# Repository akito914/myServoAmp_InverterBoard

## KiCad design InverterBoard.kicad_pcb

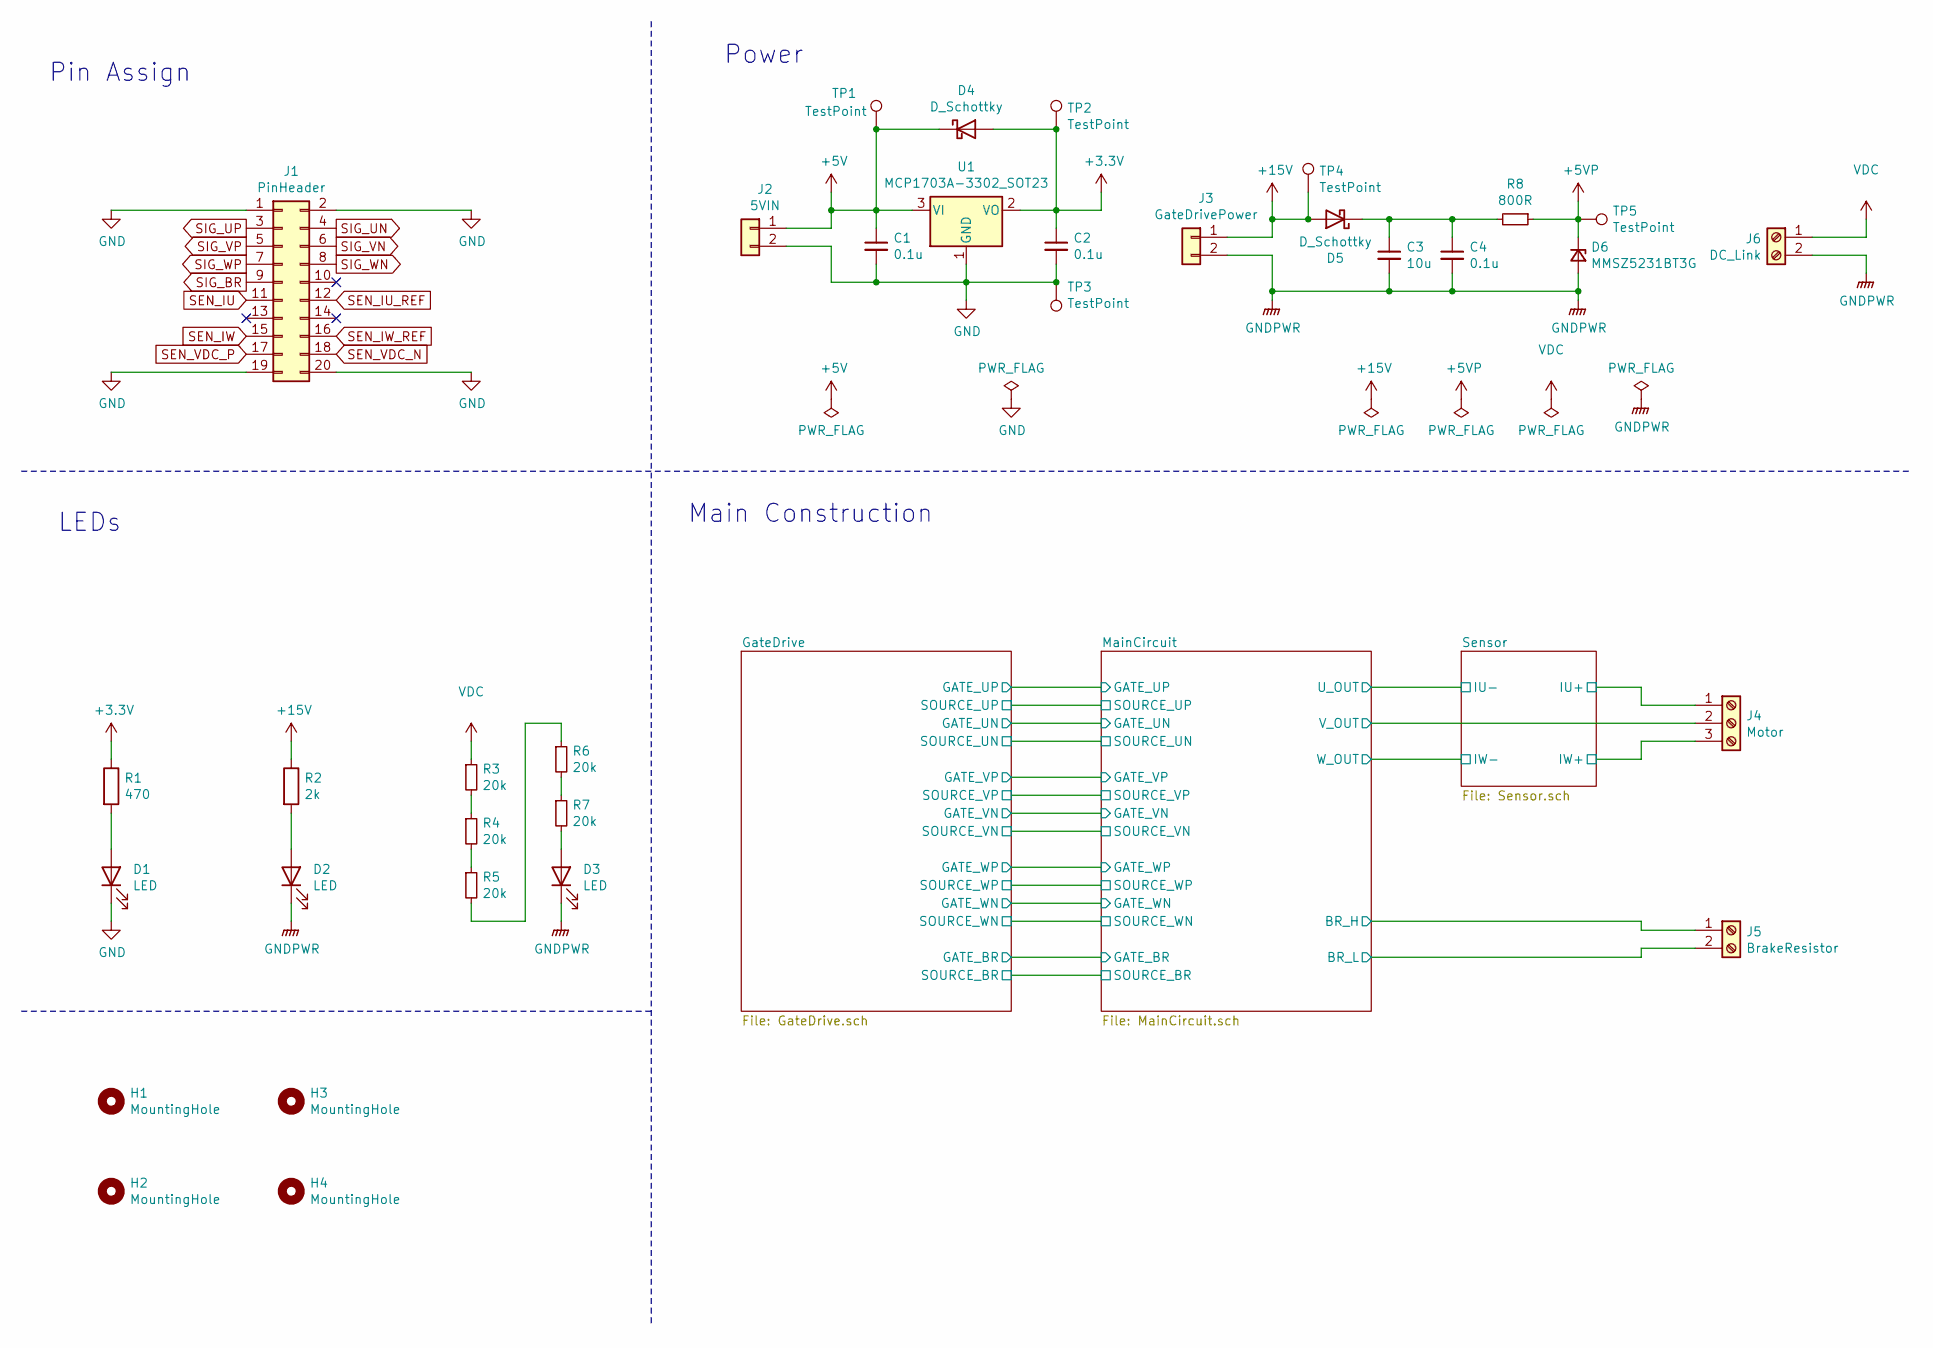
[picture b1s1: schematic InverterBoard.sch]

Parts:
C1, C2, C4: 0.1u; C_0603_1608Metric
C3: 10u; C_0805_2012Metric
D1, D2, D3: LED; LED_0603_1608Metric
D4, D5: D_Schottky; D_SOD-123
D6: MMSZ5231BT3G; D_SOD-123
H1, H2, H3, H4: MountingHole; MountingHole_3.2mm_M3
J1: PinHeader; IDC-Header_2x10_P2.54mm_Vertical
J2: 5VIN; JST_XH_S2B-XH-A-1_1x02_P2.50mm_Horizontal
J3: GateDrivePower; JST_XH_S2B-XH-A-1_1x02_P2.50mm_Horizontal
J4: Motor; JST_VH_B3PS-VH_1x03_P3.96mm_Horizontal
J5: BrakeResistor; JST_VH_B2PS-VH_1x02_P3.96mm_Horizontal
J6: DC_Link; JST_VH_B2PS-VH_1x02_P3.96mm_Horizontal
R1: 470; R_0603_1608Metric
R2: 2k; R_0603_1608Metric
R3, R4, R5, R6, R7: 20k; R_0603_1608Metric
R8: 800R; R_0603_1608Metric
TP1, TP2, TP3, TP4: TestPoint; TestPoint_Loop_D2.50mm_Drill1.0mm_LowProfile
TP5: TestPoint; TestPoint_Pad_D1.0mm
U1: MCP1703A-3302_SOT23; SOT-23

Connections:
+3V3: C2.1, D4.2 (A), R1.1, TP2.1, U1.2 (VO); also elsewhere on the board
+5V: C1.1, D4.1 (K), J2.1, TP1.1, U1.3 (VI)
+5VP: D6.1 (K), R8.1, TP5.1; also elsewhere on the board
+15V: D5.2 (A), J3.1, R2.1, TP4.1; also elsewhere on the board
/GateDrive/SOURCE_VP: J4.2; also elsewhere on the board
/MainCircuit/BR_L: J5.2; also elsewhere on the board
/Sensor/IU+: J4.1; also elsewhere on the board
/Sensor/IW+: J4.3; also elsewhere on the board
GND: C1.2, C2.2, D1.1 (K), J1.1, J1.2, J1.19, J1.20, J2.2, TP3.1, U1.1 (GND); also elsewhere on the board
GNDPWR: C3.2, C4.2, D2.1 (K), D3.1 (K), D6.2 (A), J3.2, J6.2; also elsewhere on the board
unnamed: C3.1, C4.1, D5.1 (K), R8.2
unnamed: D1.2 (A), R1.2
unnamed: D2.2 (A), R2.2
unnamed: D3.2 (A), R7.2
unnamed: R3.2, R4.1
unnamed: R4.2, R5.1
unnamed: R5.2, R6.1
unnamed: R6.2, R7.1
SEN_IU: J1.11; also elsewhere on the board
SEN_IU_REF: J1.12; also elsewhere on the board
SEN_IW: J1.15; also elsewhere on the board
SEN_IW_REF: J1.16; also elsewhere on the board
SEN_VDC_N: J1.18; also elsewhere on the board
SEN_VDC_P: J1.17; also elsewhere on the board
SIG_BR: J1.9; also elsewhere on the board
SIG_UN: J1.4; also elsewhere on the board
SIG_UP: J1.3; also elsewhere on the board
SIG_VN: J1.6; also elsewhere on the board
SIG_VP: J1.5; also elsewhere on the board
SIG_WN: J1.8; also elsewhere on the board
SIG_WP: J1.7; also elsewhere on the board
VDC: J5.1, J6.1, R3.1; also elsewhere on the board

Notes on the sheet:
Power
Main Construction
Pin Assign
LEDs

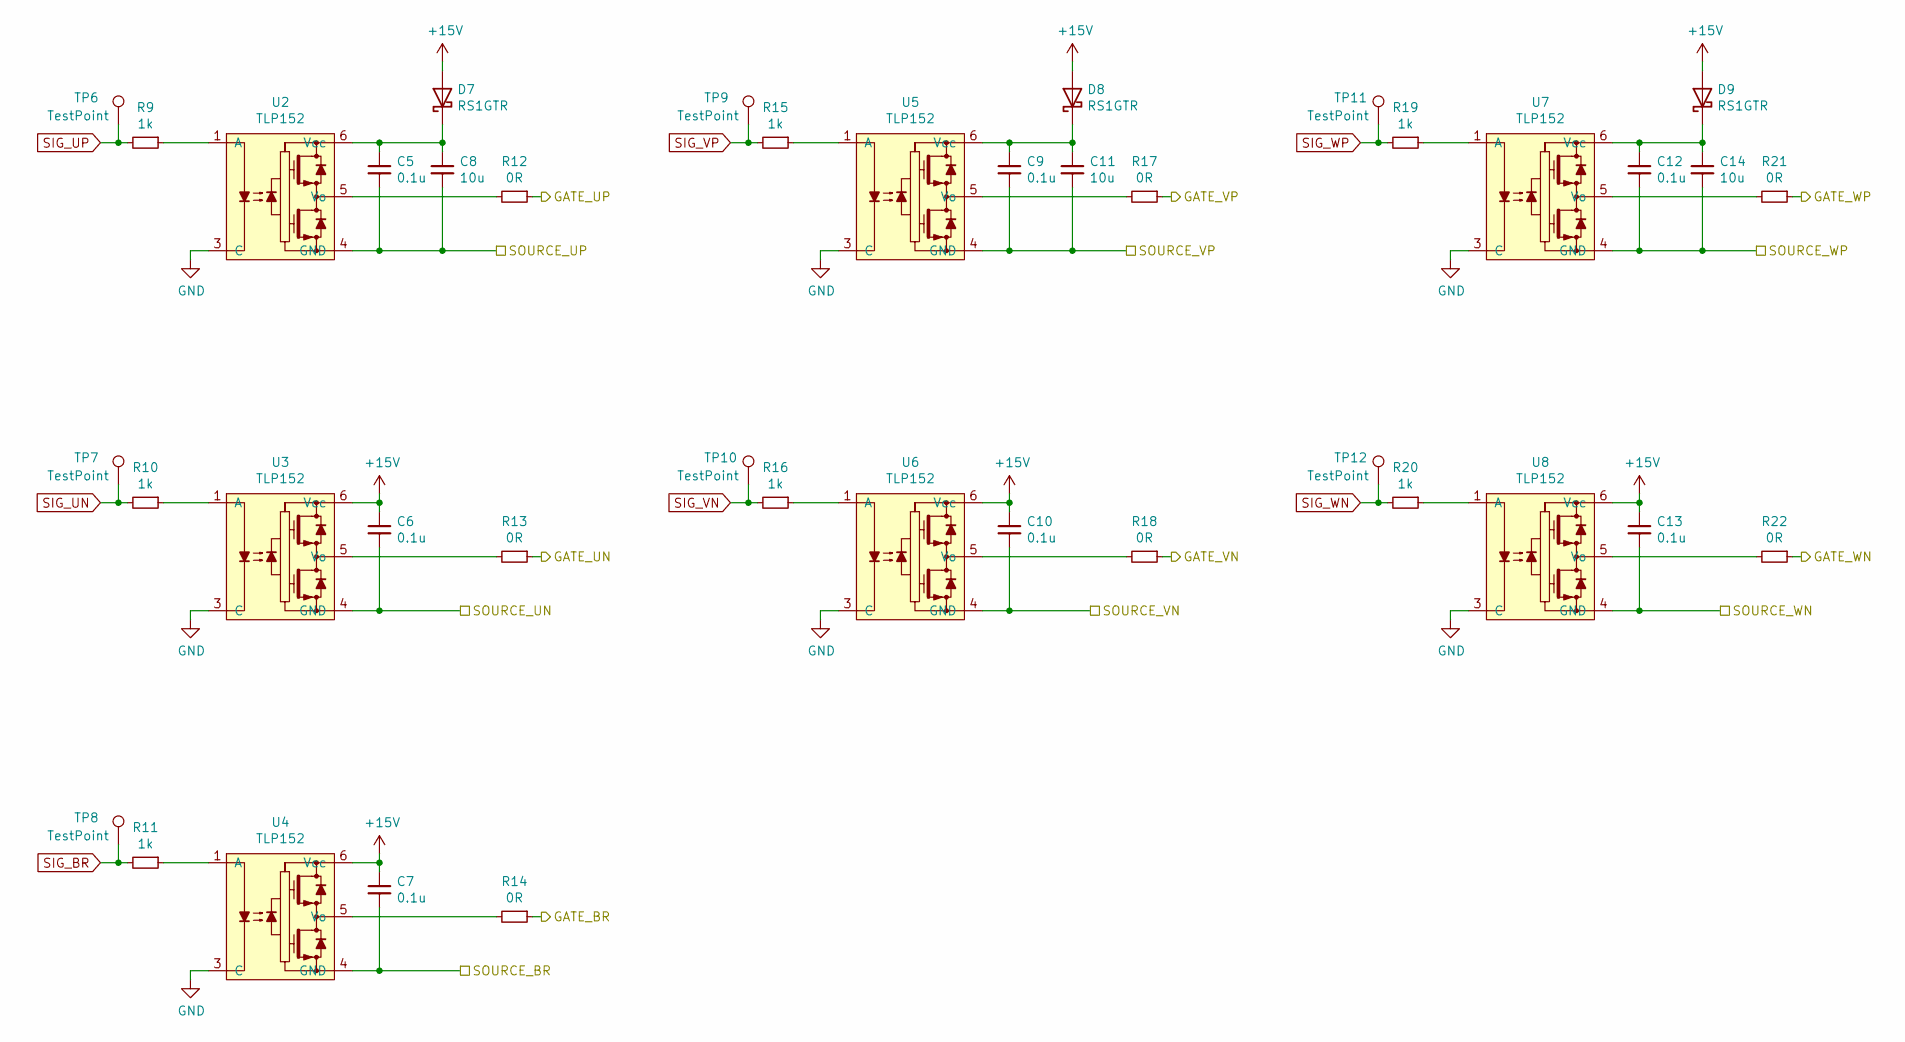
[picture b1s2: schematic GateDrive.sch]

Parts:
C5, C6, C7, C9, C10, C12, C13: 0.1u; C_0603_1608Metric
C8, C11, C14: 10u; C_0805_2012Metric
D7, D8, D9: RS1GTR; D_SMA
R9, R10, R11, R15, R16, R19, R20: 1k; R_0603_1608Metric
R12, R13, R14, R17, R18, R21, R22: 0R; R_0603_1608Metric
TP6, TP7, TP8, TP9, TP10, TP11, TP12: TestPoint; TestPoint_Pad_D1.0mm
U2, U3, U4, U5, U6, U7, U8: TLP152; SO-5_4.4x3.6mm_P1.27mm

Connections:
+15V: C6.1, C7.1, C10.1, C13.1, D7.2 (A), D8.2 (A), D9.2 (A), U3.6 (Vcc), U4.6 (Vcc), U6.6 (Vcc), U8.6 (Vcc); also elsewhere on the board
/GateDrive/GATE_BR: R14.1; also elsewhere on the board
/GateDrive/GATE_UN: R13.1; also elsewhere on the board
/GateDrive/GATE_UP: R12.1; also elsewhere on the board
/GateDrive/GATE_VN: R18.1; also elsewhere on the board
/GateDrive/GATE_VP: R17.1; also elsewhere on the board
/GateDrive/GATE_WN: R22.1; also elsewhere on the board
/GateDrive/GATE_WP: R21.1; also elsewhere on the board
/GateDrive/SOURCE_VP: C9.2, C11.2, U5.4 (GND); also elsewhere on the board
/Sensor/IU-: C5.2, C8.2, U2.4 (GND); also elsewhere on the board
/Sensor/IW-: C12.2, C14.2, U7.4 (GND); also elsewhere on the board
GND: U2.3 (C), U3.3 (C), U4.3 (C), U5.3 (C), U6.3 (C), U7.3 (C), U8.3 (C); also elsewhere on the board
GNDPWR: C6.2, C7.2, C10.2, C13.2, U3.4 (GND), U4.4 (GND), U6.4 (GND), U8.4 (GND); also elsewhere on the board
unnamed: C5.1, C8.1, D7.1 (K), U2.6 (Vcc)
unnamed: C9.1, C11.1, D8.1 (K), U5.6 (Vcc)
unnamed: C12.1, C14.1, D9.1 (K), U7.6 (Vcc)
unnamed: R9.1, U2.1 (A)
unnamed: R10.1, U3.1 (A)
unnamed: R11.1, U4.1 (A)
unnamed: R12.2, U2.5 (Vo)
unnamed: R13.2, U3.5 (Vo)
unnamed: R14.2, U4.5 (Vo)
unnamed: R15.1, U5.1 (A)
unnamed: R16.1, U6.1 (A)
unnamed: R17.2, U5.5 (Vo)
unnamed: R18.2, U6.5 (Vo)
unnamed: R19.1, U7.1 (A)
unnamed: R20.1, U8.1 (A)
unnamed: R21.2, U7.5 (Vo)
unnamed: R22.2, U8.5 (Vo)
SIG_BR: R11.2, TP8.1; also elsewhere on the board
SIG_UN: R10.2, TP7.1; also elsewhere on the board
SIG_UP: R9.2, TP6.1; also elsewhere on the board
SIG_VN: R16.2, TP10.1; also elsewhere on the board
SIG_VP: R15.2, TP9.1; also elsewhere on the board
SIG_WN: R20.2, TP12.1; also elsewhere on the board
SIG_WP: R19.2, TP11.1; also elsewhere on the board

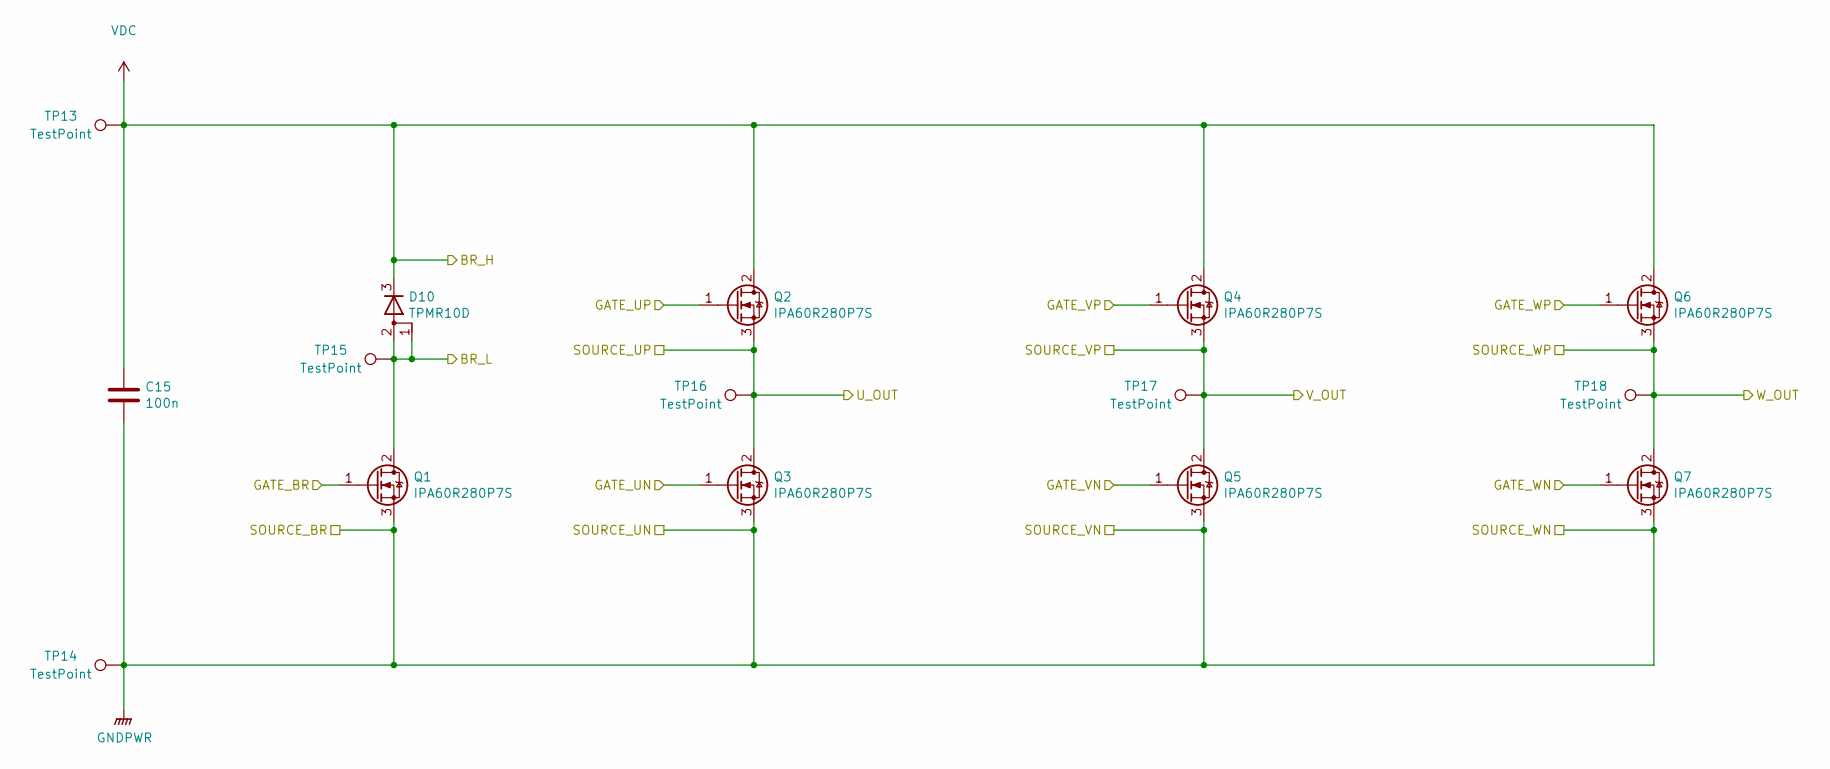
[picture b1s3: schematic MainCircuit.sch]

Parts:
C15: 100n; C_Rect_L13.0mm_W6.0mm_P10.00mm_FKS3_FKP3_MKS4
D10: TPMR10D; TO-277A
Q1, Q2, Q3, Q4, Q5, Q6, Q7: IPA60R280P7S; TO-220F-3_Horizontal_TabUp
TP13, TP14, TP15, TP16, TP17, TP18: TestPoint; TestPoint_Loop_D2.50mm_Drill1.0mm_LowProfile

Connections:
/GateDrive/GATE_BR: Q1.1 (G); also elsewhere on the board
/GateDrive/GATE_UN: Q3.1 (G); also elsewhere on the board
/GateDrive/GATE_UP: Q2.1 (G); also elsewhere on the board
/GateDrive/GATE_VN: Q5.1 (G); also elsewhere on the board
/GateDrive/GATE_VP: Q4.1 (G); also elsewhere on the board
/GateDrive/GATE_WN: Q7.1 (G); also elsewhere on the board
/GateDrive/GATE_WP: Q6.1 (G); also elsewhere on the board
/GateDrive/SOURCE_VP: Q4.3 (S), Q5.2 (D), TP17.1; also elsewhere on the board
/MainCircuit/BR_L: D10.1 (A), D10.2 (A), Q1.2 (D), TP15.1; also elsewhere on the board
/Sensor/IU-: Q2.3 (S), Q3.2 (D), TP16.1; also elsewhere on the board
/Sensor/IW-: Q6.3 (S), Q7.2 (D), TP18.1; also elsewhere on the board
GNDPWR: C15.2, Q1.3 (S), Q3.3 (S), Q5.3 (S), Q7.3 (S), TP14.1; also elsewhere on the board
VDC: C15.1, D10.3 (K), Q2.2 (D), Q4.2 (D), Q6.2 (D), TP13.1; also elsewhere on the board

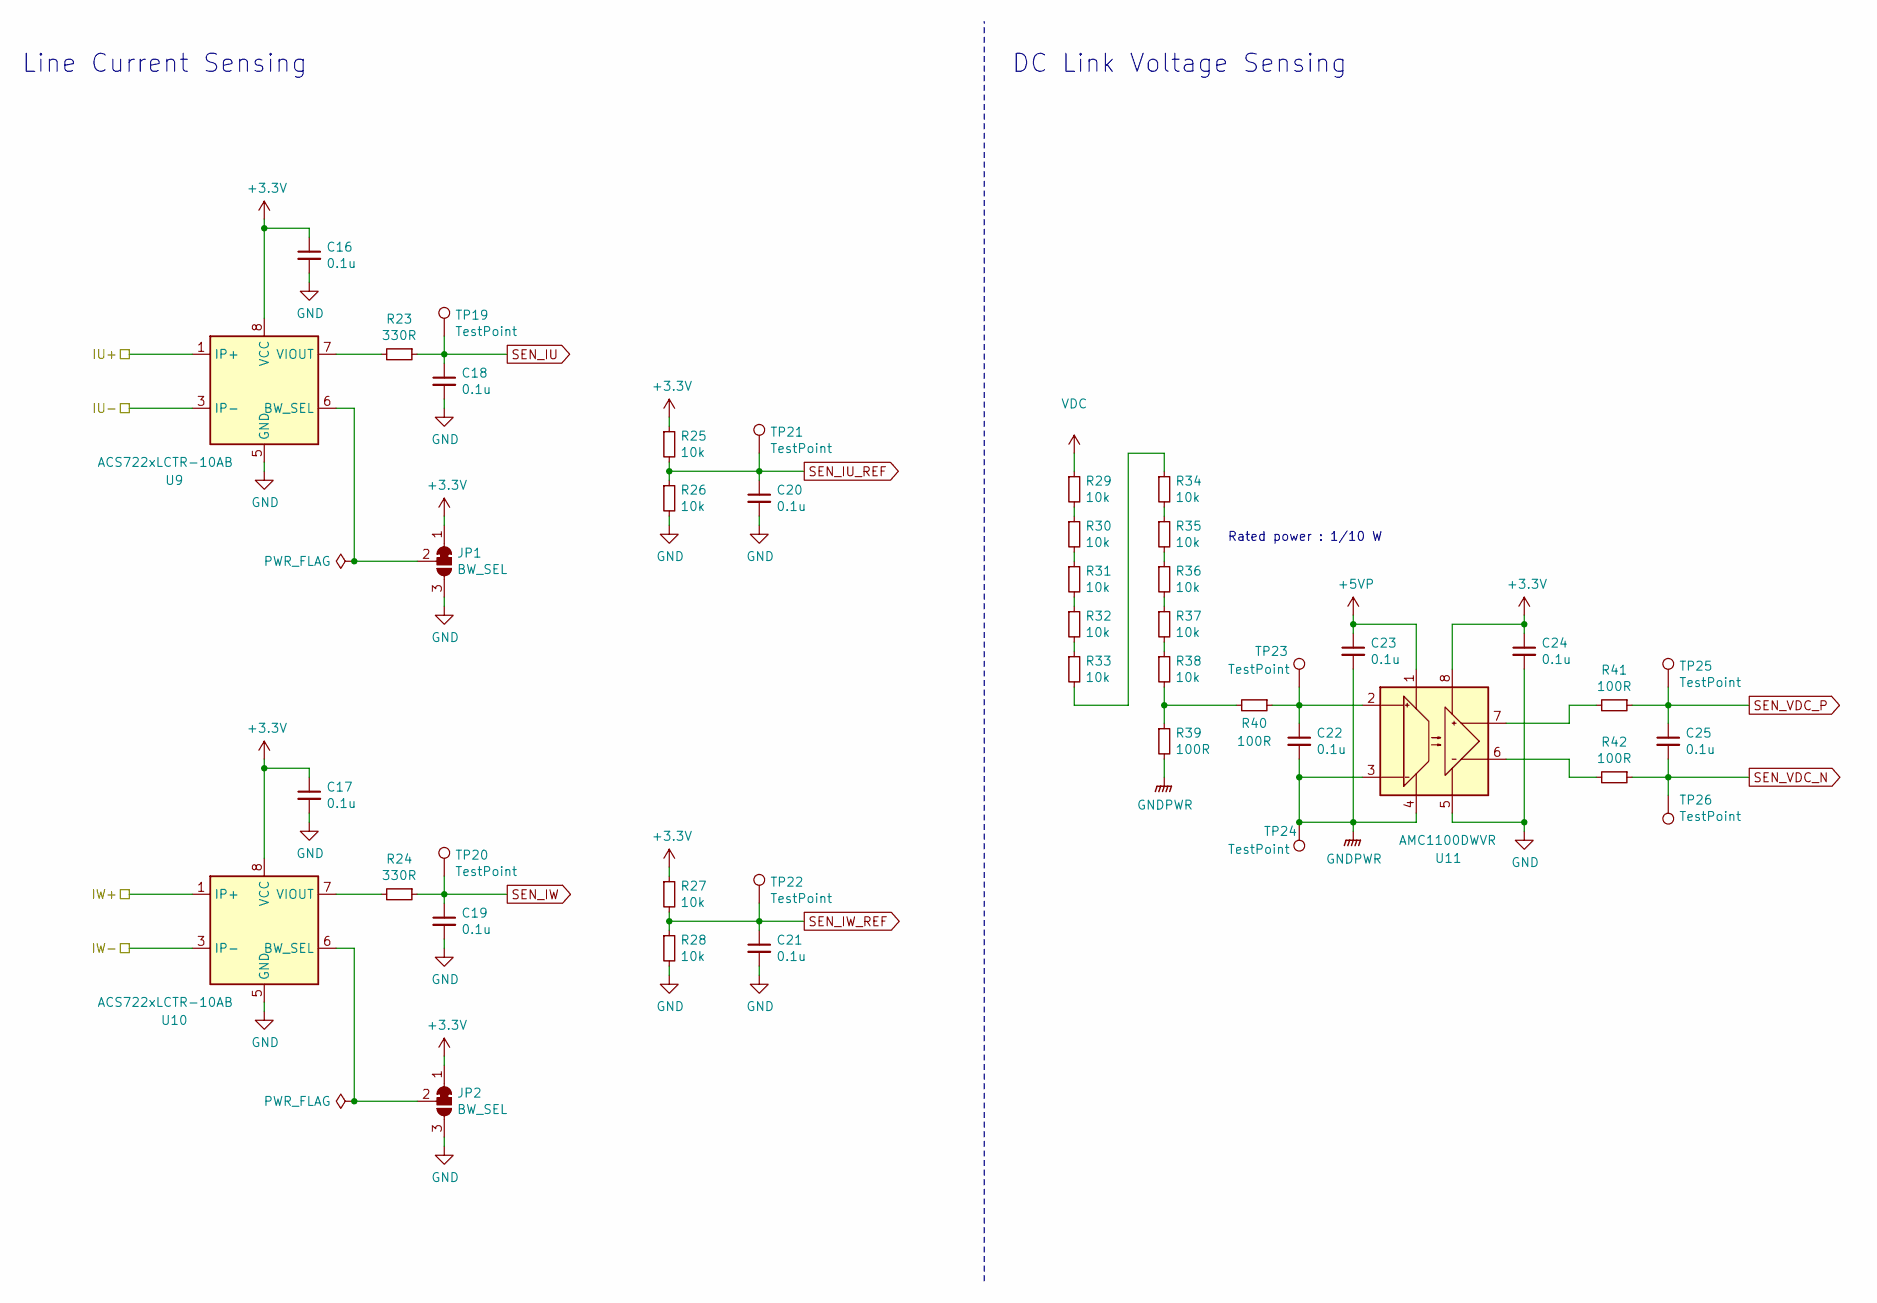
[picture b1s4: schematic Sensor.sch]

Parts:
C16, C17, C18, C19, C20, C21, C22, C23, C24, C25: 0.1u; C_0603_1608Metric
JP1, JP2: BW_SEL; SolderJumper-3_P1.3mm_Bridged12_RoundedPad1.0x1.5mm_NumberL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
R23, R24: 330R; R_0603_1608Metric
R25, R26, R27, R28, R29, R30, R31, R32, R33, R34, R35, R36, R37, R38: 10k; R_0603_1608Metric
R39, R40, R41, R42: 100R; R_0603_1608Metric
TP19, TP20, TP21, TP22, TP23, TP25, TP26: TestPoint; TestPoint_Pad_D1.0mm
TP24: TestPoint; TestPoint_Loop_D2.50mm_Drill1.0mm_LowProfile
U9, U10: ACS722xLCTR-10AB; SOIC-8_3.9x4.9mm_P1.27mm
U11: AMC1100DWVR; SOIC-8_7.5x5.85mm_P1.27mm

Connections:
+3V3: C16.1, C17.1, C24.1, JP1.1 (A), JP2.1 (A), R25.1, R27.1, U9.8 (VCC), U10.8 (VCC), U11.8 (VDD2); also elsewhere on the board
+5VP: C23.1, U11.1 (VDD1); also elsewhere on the board
/Sensor/IU+: U9.1 (IP+), U9.2 (IP+); also elsewhere on the board
/Sensor/IU-: U9.3 (IP-), U9.4 (IP-); also elsewhere on the board
/Sensor/IW+: U10.1 (IP+), U10.2 (IP+); also elsewhere on the board
/Sensor/IW-: U10.3 (IP-), U10.4 (IP-); also elsewhere on the board
GND: C16.2, C17.2, C18.2, C19.2, C20.2, C21.2, C24.2, JP1.3 (B), JP2.3 (B), R26.2, R28.2, U9.5 (GND), U10.5 (GND), U11.5 (GND2); also elsewhere on the board
GNDPWR: C22.2, C23.2, R39.2, TP24.1, U11.3 (IN-), U11.4 (GND1); also elsewhere on the board
unnamed: C22.1, R40.1, TP23.1, U11.2 (IN+)
unnamed: JP1.2 (C), U9.6 (BW_SEL)
unnamed: JP2.2 (C), U10.6 (BW_SEL)
unnamed: R23.2, U9.7 (VIOUT)
unnamed: R24.2, U10.7 (VIOUT)
unnamed: R29.2, R30.1
unnamed: R30.2, R31.1
unnamed: R31.2, R32.1
unnamed: R32.2, R33.1
unnamed: R33.2, R34.1
unnamed: R34.2, R35.1
unnamed: R35.2, R36.1
unnamed: R36.2, R37.1
unnamed: R37.2, R38.1
unnamed: R38.2, R39.1, R40.2
unnamed: R41.2, U11.7 (OUT+)
unnamed: R42.2, U11.6 (OUT-)
SEN_IU: C18.1, R23.1, TP19.1; also elsewhere on the board
SEN_IU_REF: C20.1, R25.2, R26.1, TP21.1; also elsewhere on the board
SEN_IW: C19.1, R24.1, TP20.1; also elsewhere on the board
SEN_IW_REF: C21.1, R27.2, R28.1, TP22.1; also elsewhere on the board
SEN_VDC_N: C25.2, R42.1, TP26.1; also elsewhere on the board
SEN_VDC_P: C25.1, R41.1, TP25.1; also elsewhere on the board
VDC: R29.1; also elsewhere on the board

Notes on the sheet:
Rated power : 1/10 W
DC Link Voltage Sensing
Line Current Sensing

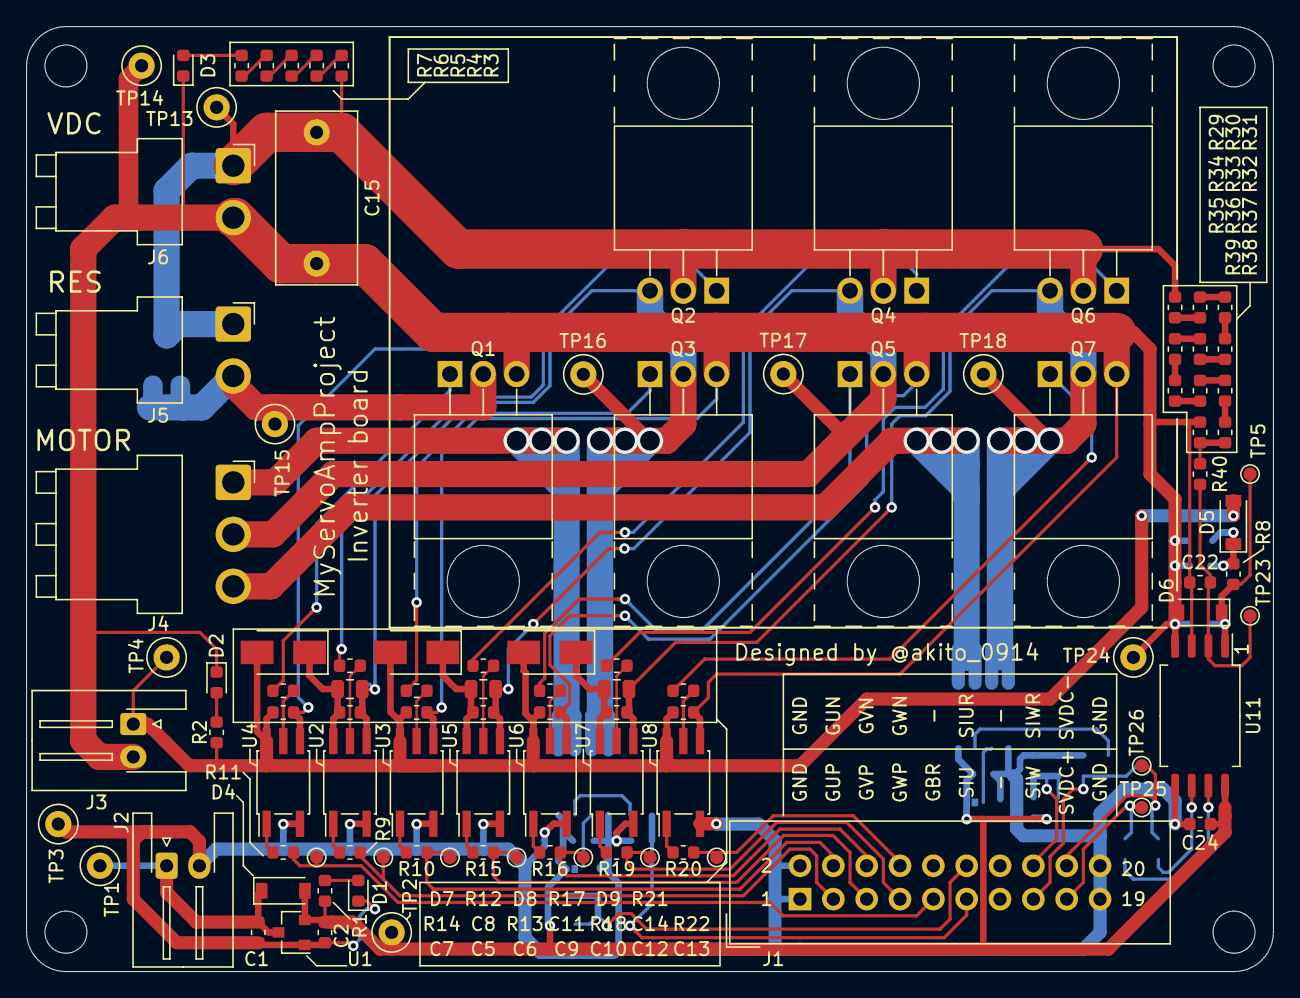
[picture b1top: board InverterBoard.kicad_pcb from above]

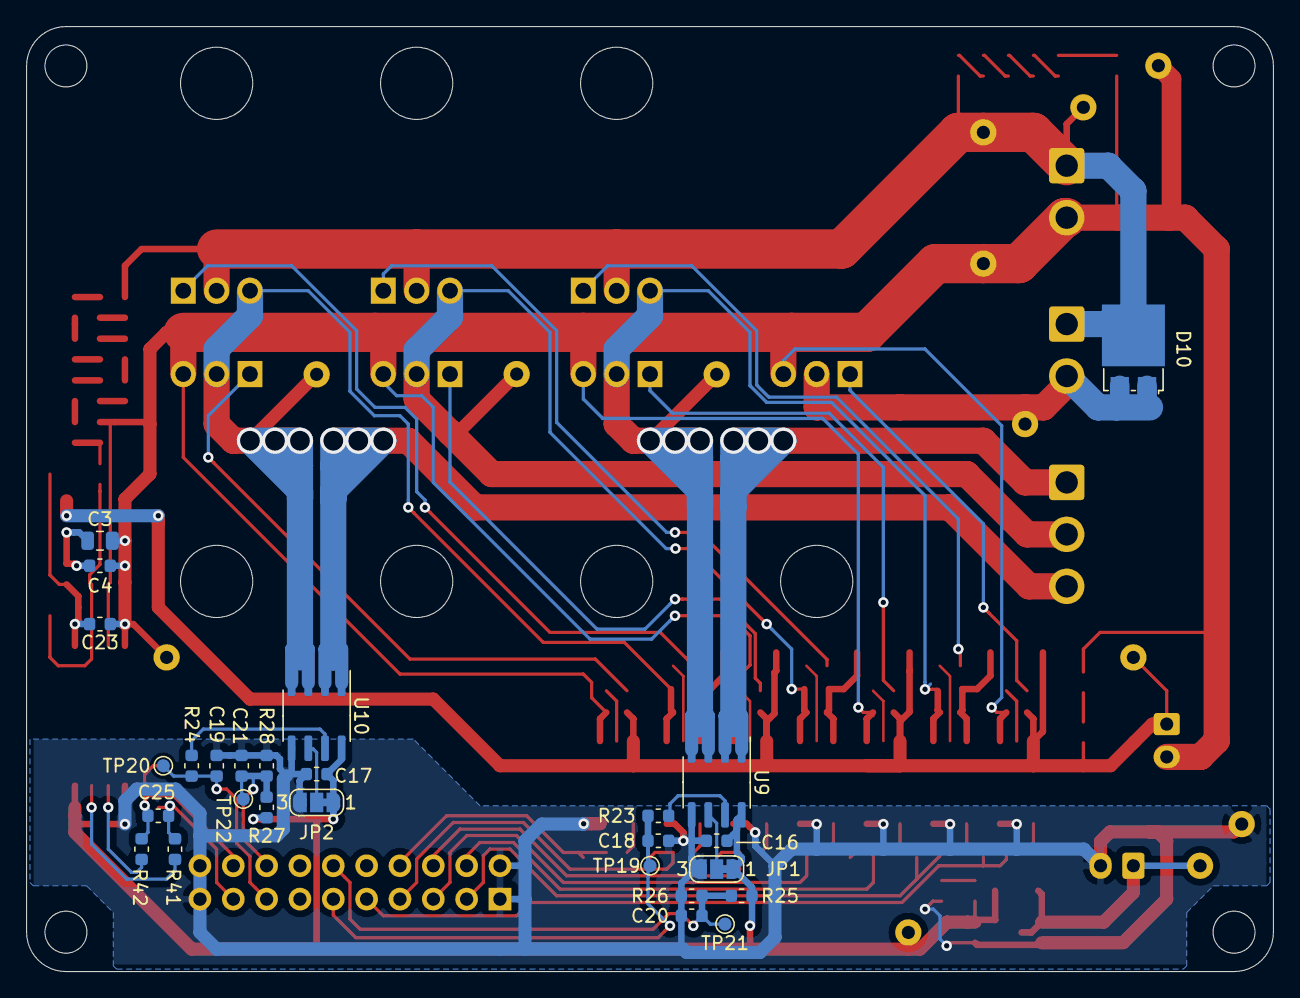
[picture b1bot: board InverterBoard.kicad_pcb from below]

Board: 2 copper layers, 95.0 x 72.0 mm, 133 parts (27 on the bottom side), 75 nets.

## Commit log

2020-04-05 回路図完成、アートワーク主回路まで
2020-04-07 アートワークも一応完成
2020-04-07 TODO削除
2020-04-10 テストポイント追加，シルク調整，固定穴マスク追加
2020-04-11 GNDベタ追加，電流センサ周辺部品の配置調整
2020-04-11 DCリンクのフィルムキャパシタの値修正
2020-04-16 配線ちょっと修正
2020-04-21 ガーバー吐き出し
2020-04-21 Elecrow発注用ガーバー
